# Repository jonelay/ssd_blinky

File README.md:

ssd_blinky
==========

A repository for the Solid State Depot KiCAD workshop series.

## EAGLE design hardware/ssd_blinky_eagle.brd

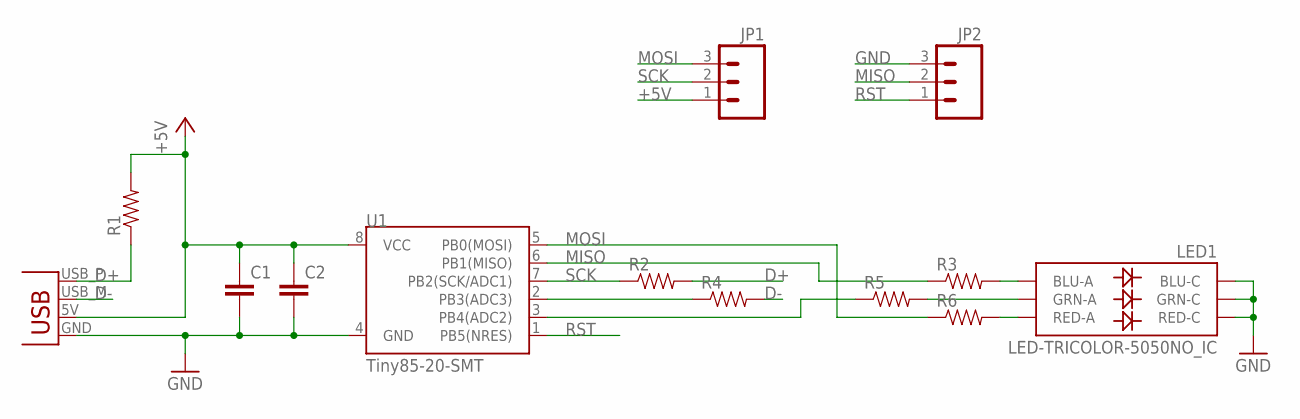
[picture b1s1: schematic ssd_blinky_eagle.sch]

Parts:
C1, C2: CAP1206; 1206
JP1, JP2: M03SMD_RA_MALE; 1X03_SMD_RA_MALE
JP3: USBPCB; USB-A-PCB
LED1: LED-TRICOLOR-5050NO_IC; LED-TRICOLOR-5050
R1, R2, R3, R4, R5, R6: RESISTOR1206; 1206
U1: Tiny85-20-SMT; SO08-EIAJ

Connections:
+5V: C1.1, C2.1, JP1.1, JP3.5V (VBUS), R1.2, U1.8 (VCC)
D+: JP3.USB_P (D+), R1.1, R2.2
D-: JP3.USB_M (D-), R4.2
GND: C1.2, C2.2, JP2.3, JP3.GND, LED1.4 (BLU-C), LED1.5 (RED-C), LED1.6 (GRN-C), U1.4 (GND)
MISO: JP2.2, R5.1, U1.3 (PB4(ADC2))
MOSI: JP1.3, R6.1, U1.5 (PB0(MOSI))
unnamed: R4.1, U1.2 (PB3(ADC3))
unnamed: R3.1, U1.6 (PB1(MISO))
unnamed: LED1.2 (RED-A), R6.2
unnamed: LED1.1 (GRN-A), R5.2
unnamed: LED1.3 (BLU-A), R3.2
RST: JP2.1, U1.1 (PB5(NRES))
SCK: JP1.2, R2.1, U1.7 (PB2(SCK/ADC1))

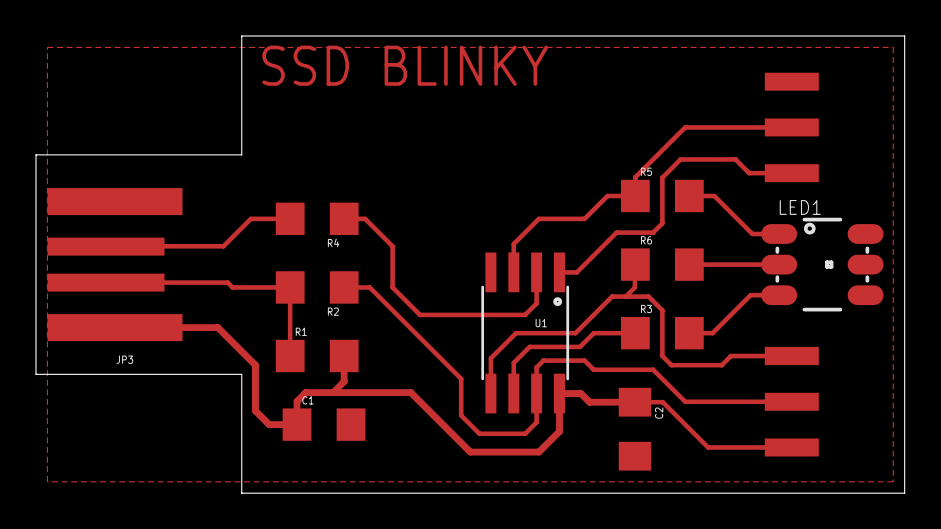
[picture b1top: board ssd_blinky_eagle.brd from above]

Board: 2 copper layers, 48.3 x 25.4 mm, 13 parts (0 on the bottom side), 13 nets.

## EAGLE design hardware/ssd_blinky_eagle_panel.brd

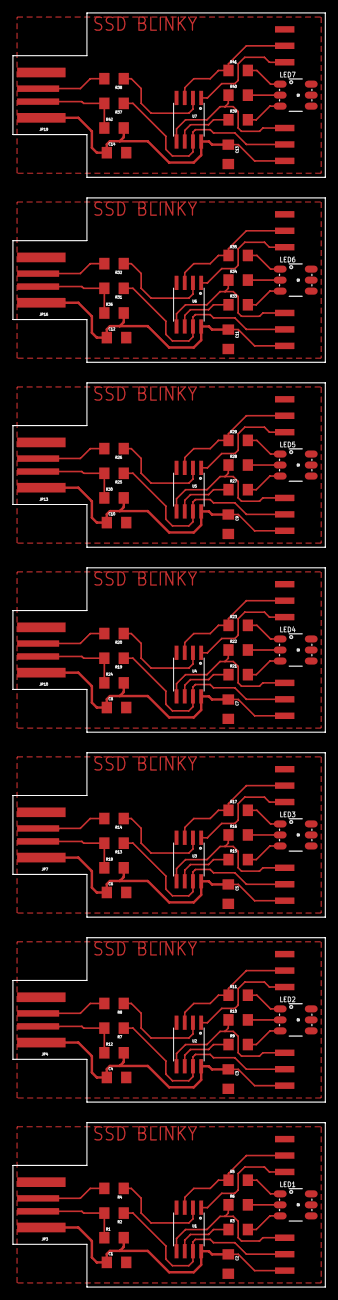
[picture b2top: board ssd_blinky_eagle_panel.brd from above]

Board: 2 copper layers, 48.3 x 196.8 mm, 91 parts (0 on the bottom side), 91 nets.

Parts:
C1, C2, C3, C4, C5, C6, C7, C8, C9, C10, C11, C12, C13, C14: 1206
JP1, JP2, JP5, JP6, JP8, JP9, JP11, JP12, JP14, JP15, JP17, JP18, JP20, JP21: 1X03_SMD_RA_MALE
JP3, JP4, JP7, JP10, JP13, JP16, JP19: USBPCB; USB-A-PCB
LED1, LED2, LED3, LED4, LED5, LED6, LED7: LED-TRICOLOR-5050NO_IC; LED-TRICOLOR-5050
R1, R2, R3, R4, R5, R6, R7, R8, R9, R10, R11, R12, R13, R14, R15, R16, R17, R18, R19, R20, R21, R22, R23, R24, R25, R26, R27, R28, R29, R30, R31, R32, R33, R34, R35, R36, R37, R38, R39, R40, R41, R42: 1206
U1, U2, U3, U4, U5, U6, U7: Tiny85-20-SMT; SO08-EIAJ

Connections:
+5V: C1.1, C2.1, JP1.1, JP3.5V, R1.2, U1.8
+5V1: C3.1, C4.1, JP4.5V, JP5.1, R12.2, U2.8
+5V2: C5.1, C6.1, JP7.5V, JP8.1, R18.2, U3.8
+5V3: C7.1, C8.1, JP10.5V, JP11.1, R24.2, U4.8
+5V4: C9.1, C10.1, JP13.5V, JP14.1, R30.2, U5.8
+5V5: C11.1, C12.1, JP16.5V, JP17.1, R36.2, U6.8
+5V6: C13.1, C14.1, JP19.5V, JP20.1, R42.2, U7.8
D+: JP3.USB_P, R1.1, R2.2
D+1: JP4.USB_P, R7.2, R12.1
D+2: JP7.USB_P, R13.2, R18.1
D+3: JP10.USB_P, R19.2, R24.1
D+4: JP13.USB_P, R25.2, R30.1
D+5: JP16.USB_P, R31.2, R36.1
D+6: JP19.USB_P, R37.2, R42.1
D-: JP3.USB_M, R4.2
D-1: JP4.USB_M, R8.2
D-2: JP7.USB_M, R14.2
D-3: JP10.USB_M, R20.2
D-4: JP13.USB_M, R26.2
D-5: JP16.USB_M, R32.2
D-6: JP19.USB_M, R38.2
GND: C1.2, C2.2, JP2.3, JP3.GND, LED1.4, LED1.5, LED1.6, U1.4
GND1: C3.2, C4.2, JP4.GND, JP6.3, LED2.4, LED2.5, LED2.6, U2.4
GND2: C5.2, C6.2, JP7.GND, JP9.3, LED3.4, LED3.5, LED3.6, U3.4
GND3: C7.2, C8.2, JP10.GND, JP12.3, LED4.4, LED4.5, LED4.6, U4.4
GND4: C9.2, C10.2, JP13.GND, JP15.3, LED5.4, LED5.5, LED5.6, U5.4
GND5: C11.2, C12.2, JP16.GND, JP18.3, LED6.4, LED6.5, LED6.6, U6.4
GND6: C13.2, C14.2, JP19.GND, JP21.3, LED7.4, LED7.5, LED7.6, U7.4
MISO: JP2.2, R5.1, U1.3
MISO1: JP6.2, R11.1, U2.3
MISO2: JP9.2, R17.1, U3.3
MISO3: JP12.2, R23.1, U4.3
MISO4: JP15.2, R29.1, U5.3
MISO5: JP18.2, R35.1, U6.3
MISO6: JP21.2, R41.1, U7.3
MOSI: JP1.3, R6.1, U1.5
MOSI1: JP5.3, R10.1, U2.5
MOSI2: JP8.3, R16.1, U3.5
MOSI3: JP11.3, R22.1, U4.5
MOSI4: JP14.3, R28.1, U5.5
MOSI5: JP17.3, R34.1, U6.5
MOSI6: JP20.3, R40.1, U7.5
unnamed: R4.1, U1.2
unnamed: R3.1, U1.6
unnamed: LED2.2, R10.2
unnamed: LED1.2, R6.2
unnamed: LED1.1, R5.2
unnamed: LED1.3, R3.2
unnamed: LED2.1, R11.2
unnamed: LED2.3, R9.2
unnamed: R8.1, U2.2
unnamed: R9.1, U2.6
unnamed: LED3.2, R16.2
unnamed: LED3.1, R17.2
unnamed: LED3.3, R15.2
unnamed: R14.1, U3.2
unnamed: R15.1, U3.6
unnamed: LED4.2, R22.2
unnamed: LED4.1, R23.2
unnamed: LED4.3, R21.2
unnamed: R20.1, U4.2
unnamed: R21.1, U4.6
unnamed: LED5.2, R28.2
unnamed: LED5.1, R29.2
unnamed: LED5.3, R27.2
unnamed: R26.1, U5.2
unnamed: R27.1, U5.6
unnamed: LED6.2, R34.2
unnamed: LED6.1, R35.2
unnamed: LED6.3, R33.2
unnamed: R32.1, U6.2
unnamed: R33.1, U6.6
unnamed: LED7.2, R40.2
unnamed: LED7.1, R41.2
unnamed: LED7.3, R39.2
unnamed: R38.1, U7.2
unnamed: R39.1, U7.6
RST: JP2.1, U1.1
RST1: JP6.1, U2.1
RST2: JP9.1, U3.1
RST3: JP12.1, U4.1
RST4: JP15.1, U5.1
RST5: JP18.1, U6.1
RST6: JP21.1, U7.1
SCK: JP1.2, R2.1, U1.7
SCK1: JP5.2, R7.1, U2.7
SCK2: JP8.2, R13.1, U3.7
SCK3: JP11.2, R19.1, U4.7
SCK4: JP14.2, R25.1, U5.7
SCK5: JP17.2, R31.1, U6.7
SCK6: JP20.2, R37.1, U7.7

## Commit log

2014-02-23 file creation for kicad schematic, datasheets (summary and complete) for attiny85, reference design from a similar project online
2014-02-23 incremental progress on schematic
2014-02-23 added support files for schematic
2014-02-23 added RGB LED datasheet
2014-02-23 added orblink reference design files, component value calculation spreadsheet, and updated kicad design files
2014-03-02 added eagle fork of the workshop project board
2014-03-02 complete candidate board layout in eagle
2014-03-02 added outline for workshop2
2014-03-08 added panelized pcb layout for eagle, and PS file output of layout for printing
2014-03-08 mirrored the ps file to make it appropriate for the printing process

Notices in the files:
parts and their libraries:
SparkFun-DigitalIC: Licensing: CC v3.0 Share-Alike You are welcome to use this library for commercial purposes.
